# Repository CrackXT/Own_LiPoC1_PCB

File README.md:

# Own_LiPoC1_PCB

PCB files for a LiPo Cell port on a separate board 

# Description

This is an external port board that allows you to mount the wire from LiPo cell and thus have better connection and mounting options in your project or case.

The board can be produced here (AISLER) with the files (.brd and .sch) or by any other PCB manufacturer. -> https://aisler.net/

# Serie

- .pro

# Layout

Top<br>

Bottom<br>

Routing/Dimensions(inch)<br>

Schematic<br>
Schematic as .pdf at the top of the page.

# License

Open hardware, use it, mod it, whatever you want, feel free...

# Thanks!

Own design and layout.

# Version - Build

v2.0 - 06.11.2022

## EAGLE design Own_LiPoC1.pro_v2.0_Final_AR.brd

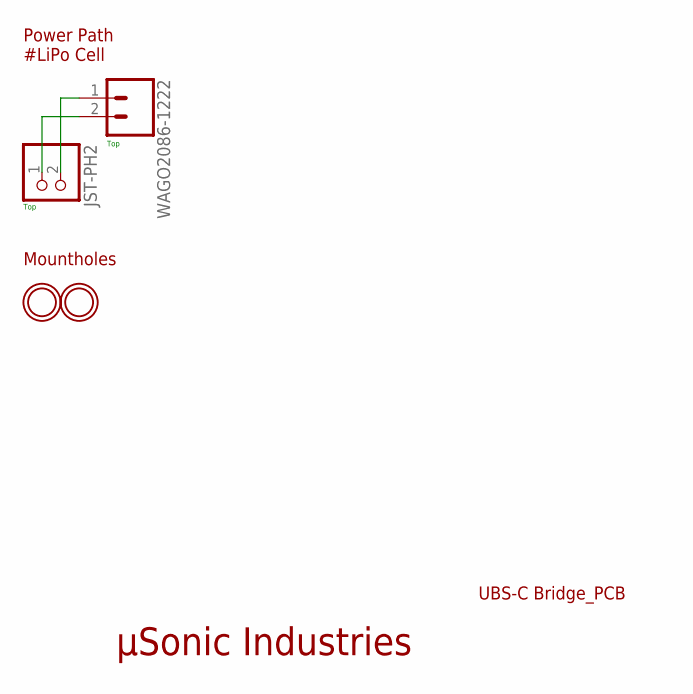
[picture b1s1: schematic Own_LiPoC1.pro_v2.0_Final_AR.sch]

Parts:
JST-PH2: JST_2PINOWN; JST-PH-2-THMOWN
U$2, U$10: MOUNTINGHOLE2.5; MOUNTINGHOLE_2.5_PLATED
WAGO2086-1222: CONN_022086-1222_KURZ; 1X02_OWN_WAGO2086-1222

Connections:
3V7: JST-PH2.1 (2), WAGO2086-1222.2
GND: JST-PH2.2 (1), WAGO2086-1222.1

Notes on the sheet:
µSonic Industries
UBS-C Bridge_PCB
Power Path #LiPo Cell
Mountholes
Top

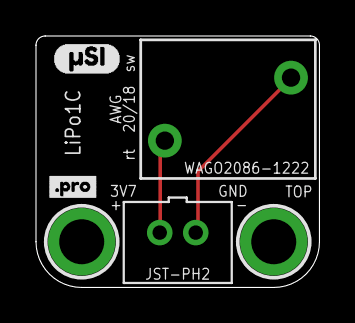
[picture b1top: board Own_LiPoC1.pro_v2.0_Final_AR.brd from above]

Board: 2 copper layers, 15.7 x 14.0 mm, 7 parts (1 on the bottom side), 2 nets.

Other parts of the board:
U$1: #SI0
U$4: OSHW-LOGO-S
U$5: #PRO0

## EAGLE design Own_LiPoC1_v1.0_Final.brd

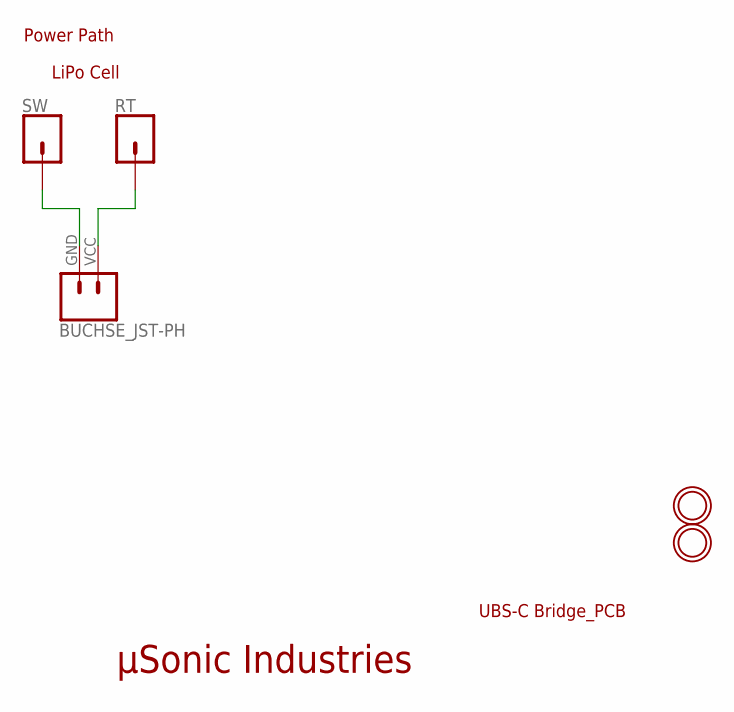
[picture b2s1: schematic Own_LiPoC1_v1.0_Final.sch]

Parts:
BUCHSE_JST-PH: CONN_024UCON-15767; JST-2-SMD-VERT
RT: CONN_01OFFSET; 1X01_OFFSET
SW: CONN_01OFFSET; 1X01_OFFSET
U$2, U$10: MOUNTINGHOLE2.5; MOUNTINGHOLE_2.5_PLATED

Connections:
3V7: BUCHSE_JST-PH.VCC (2), RT.1
GND: BUCHSE_JST-PH.GND (1), SW.1

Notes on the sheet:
µSonic Industries
UBS-C Bridge_PCB
Power Path
LiPo Cell

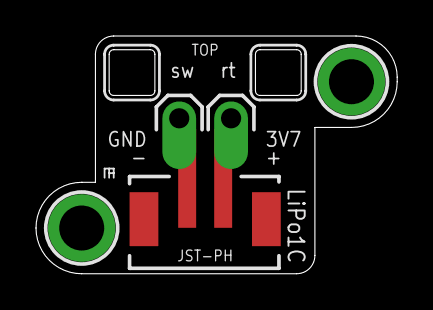
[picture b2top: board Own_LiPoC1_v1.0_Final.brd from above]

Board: 2 copper layers, 20.1 x 13.2 mm, 6 parts (1 on the bottom side), 2 nets.

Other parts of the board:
U$4: OSHW-LOGO-S

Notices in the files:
parts and their libraries:
microbuilder: This work is placed in the public domain, and may be freely used for commercial and non-commercial work with the following conditions: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
SparkFun-Aesthetics: Licensing: Creative Commons ShareAlike 4.0 International - https://creativecommons.org/licenses/by-sa/4.0
